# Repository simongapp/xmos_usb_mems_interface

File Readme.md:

# XMOS USB - MEMS microphone array audio interface
Hardware and firmware files for a MEMS microphones USB audio interface based on the XMOS XUF216. Allows to connect up to  16 microphones and provides the option to cascade multiple base boards.  

This work was done as part of my master's thesis at the TU Berlin, Department of Engineering Acoustics [https://www.akustik.tu-berlin.de/menue/home/parameter/en/](https://www.akustik.tu-berlin.de/menue/home/parameter/en/). The system was evaluated with the Acoular Framework for beamforming [http://www.acoular.org/](http://www.acoular.org/).

## Features
- Operates at 48kHz/24bit, with USB 2.0 (UAC2)
- One base board can process up to 16 MEMS microphones
- Cascade multiple baseboards by sharing a word clock or sync to external clock master
- Physically detached microphones, allows to add microphones in pairs of two
- Max. cable length between microphones and base board: 2.5m @ 48kHz
- Impedance matched clock and data transmission lines

## Folders
- 00PCB: EAGLE PCB files for the microphone PCBs and base board
- 01Firmware: XMOS firmware, port documentation and visualizations of the reference code

## Usage
- Clone to your local hard drive

- How to add the firmware files to xTimeComposer (based on https://gist.github.com/ahogen/93bf33ce47bb96c7fda60d844238fa43):  
  1. Link (but don't copy) projects and libraries from SVN dir into workspace
     1. File > Import > General > Existing Projects into Workspace
     2. Choose "Select root directory"
     3. Click "Browse" and navigate to the SVN dir where your projects and libraries were exported
     4. Click "Select All" to choose all projects and libraries
     5. Make sure "Copy projects into workspace" is not checked
     6. Finish

## Known issues
- Data transfer from the microphone boards to the base board leads to inverted data signals on the base board. Fixed by multiplying -1 on the PCM signals.
- No deterministic phase relationship between input and output of the CS2100. This results in a non-deterministic clock shift of up to 162.5ns@48kHz. Considered negligible with respect to the period of audio frequencies from 50ms(20Hz) to 42us(20kHz).
- The current firmware starts audio sampling as soon as the uC is ready, which leads to different buffer sizes and thus a delay of several samples at the host when using multiple base boards. Solution: Synchronize start of audio sampling to first SOF after device configuration. To be implemented in the future.

## License
MIT License

Copyright (c) 2021 Simon Gapp

Permission is hereby granted, free of charge, to any person obtaining a copy
of this software and associated documentation files (the "Software"), to deal
in the Software without restriction, including without limitation the rights
to use, copy, modify, merge, publish, distribute, sublicense, and/or sell
copies of the Software, and to permit persons to whom the Software is
furnished to do so, subject to the following conditions:

The above copyright notice and this permission notice shall be included in all
copies or substantial portions of the Software.

THE SOFTWARE IS PROVIDED "AS IS", WITHOUT WARRANTY OF ANY KIND, EXPRESS OR
IMPLIED, INCLUDING BUT NOT LIMITED TO THE WARRANTIES OF MERCHANTABILITY,
FITNESS FOR A PARTICULAR PURPOSE AND NONINFRINGEMENT. IN NO EVENT SHALL THE
AUTHORS OR COPYRIGHT HOLDERS BE LIABLE FOR ANY CLAIM, DAMAGES OR OTHER
LIABILITY, WHETHER IN AN ACTION OF CONTRACT, TORT OR OTHERWISE, ARISING FROM,
OUT OF OR IN CONNECTION WITH THE SOFTWARE OR THE USE OR OTHER DEALINGS IN THE
SOFTWARE.

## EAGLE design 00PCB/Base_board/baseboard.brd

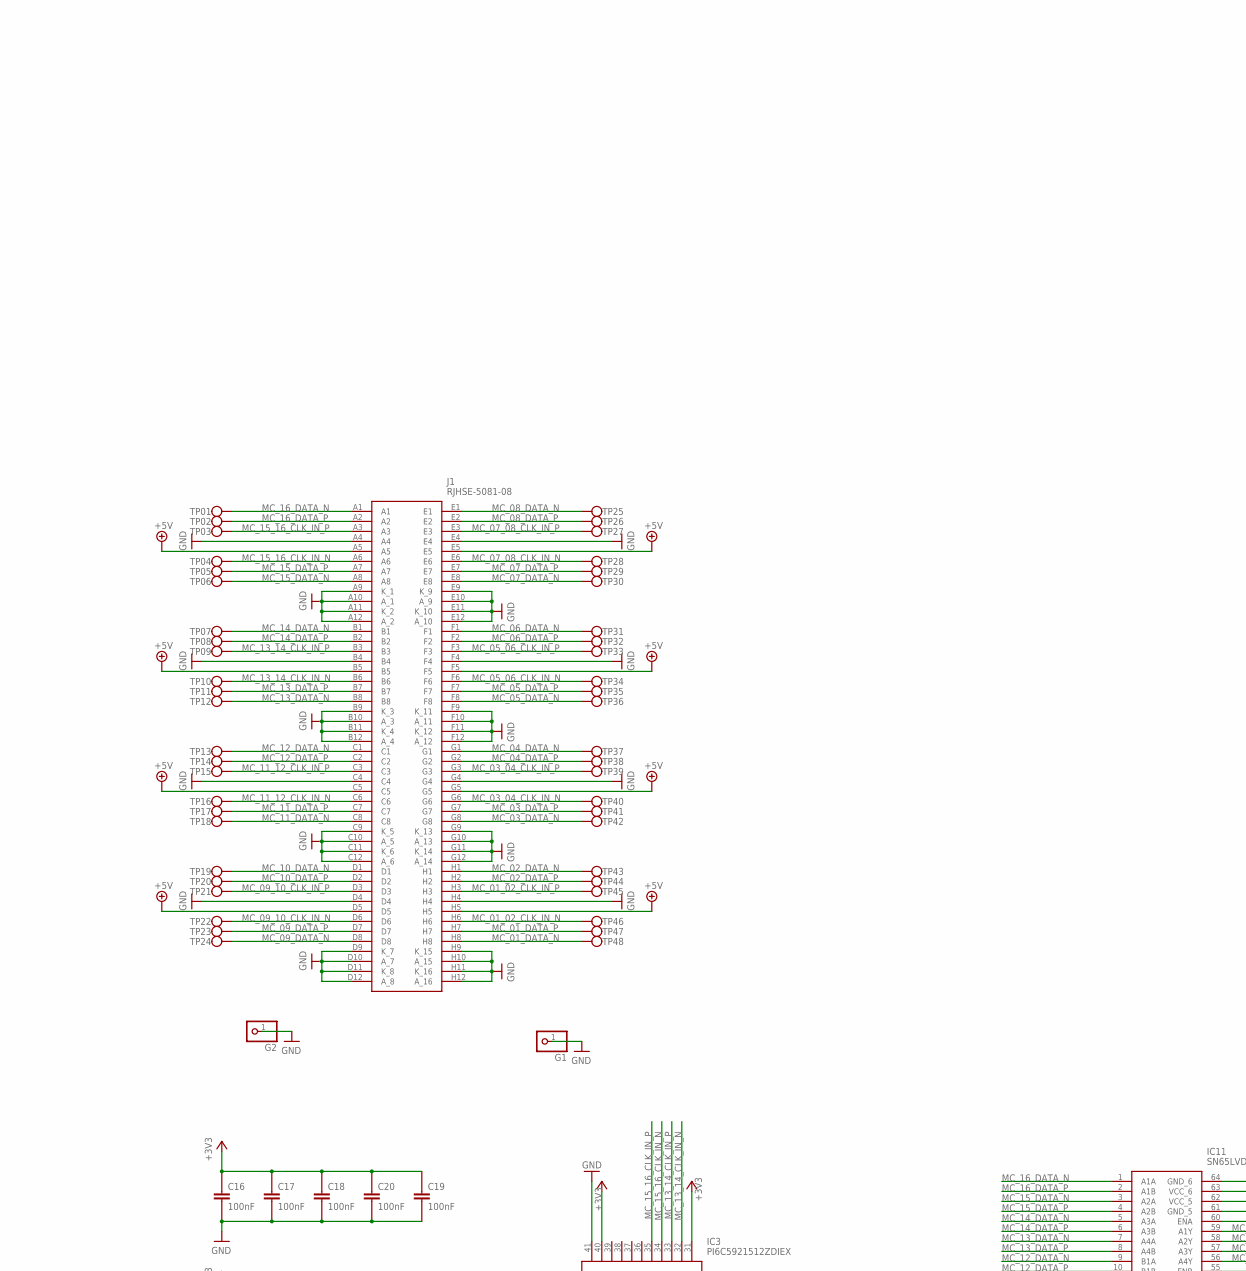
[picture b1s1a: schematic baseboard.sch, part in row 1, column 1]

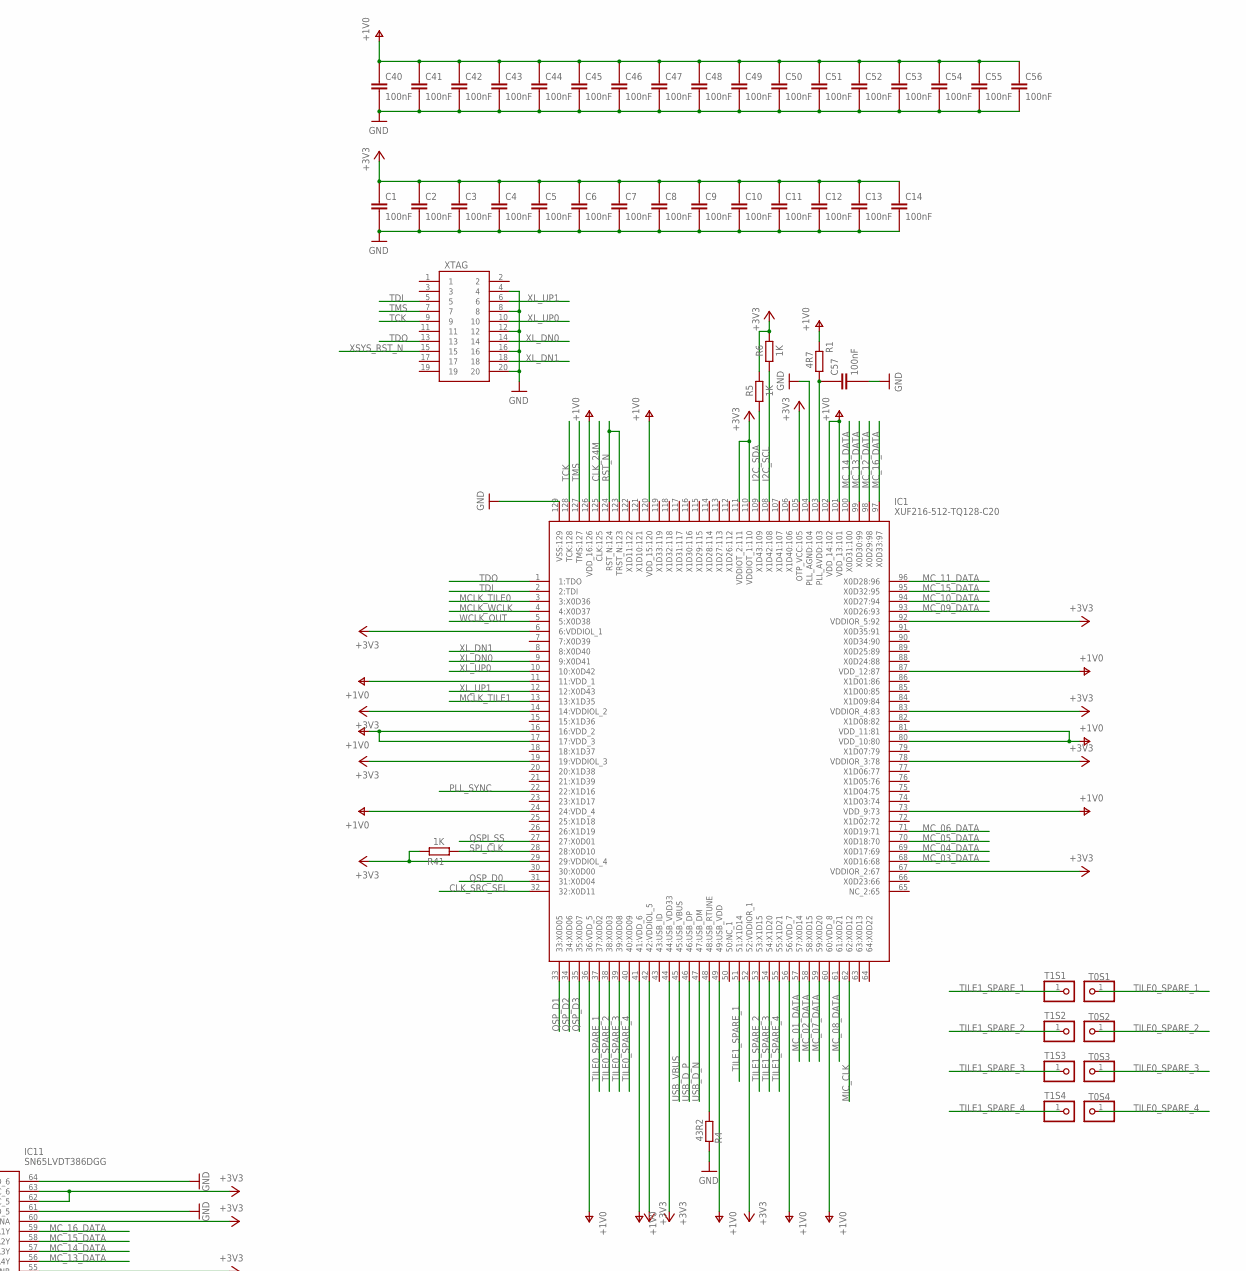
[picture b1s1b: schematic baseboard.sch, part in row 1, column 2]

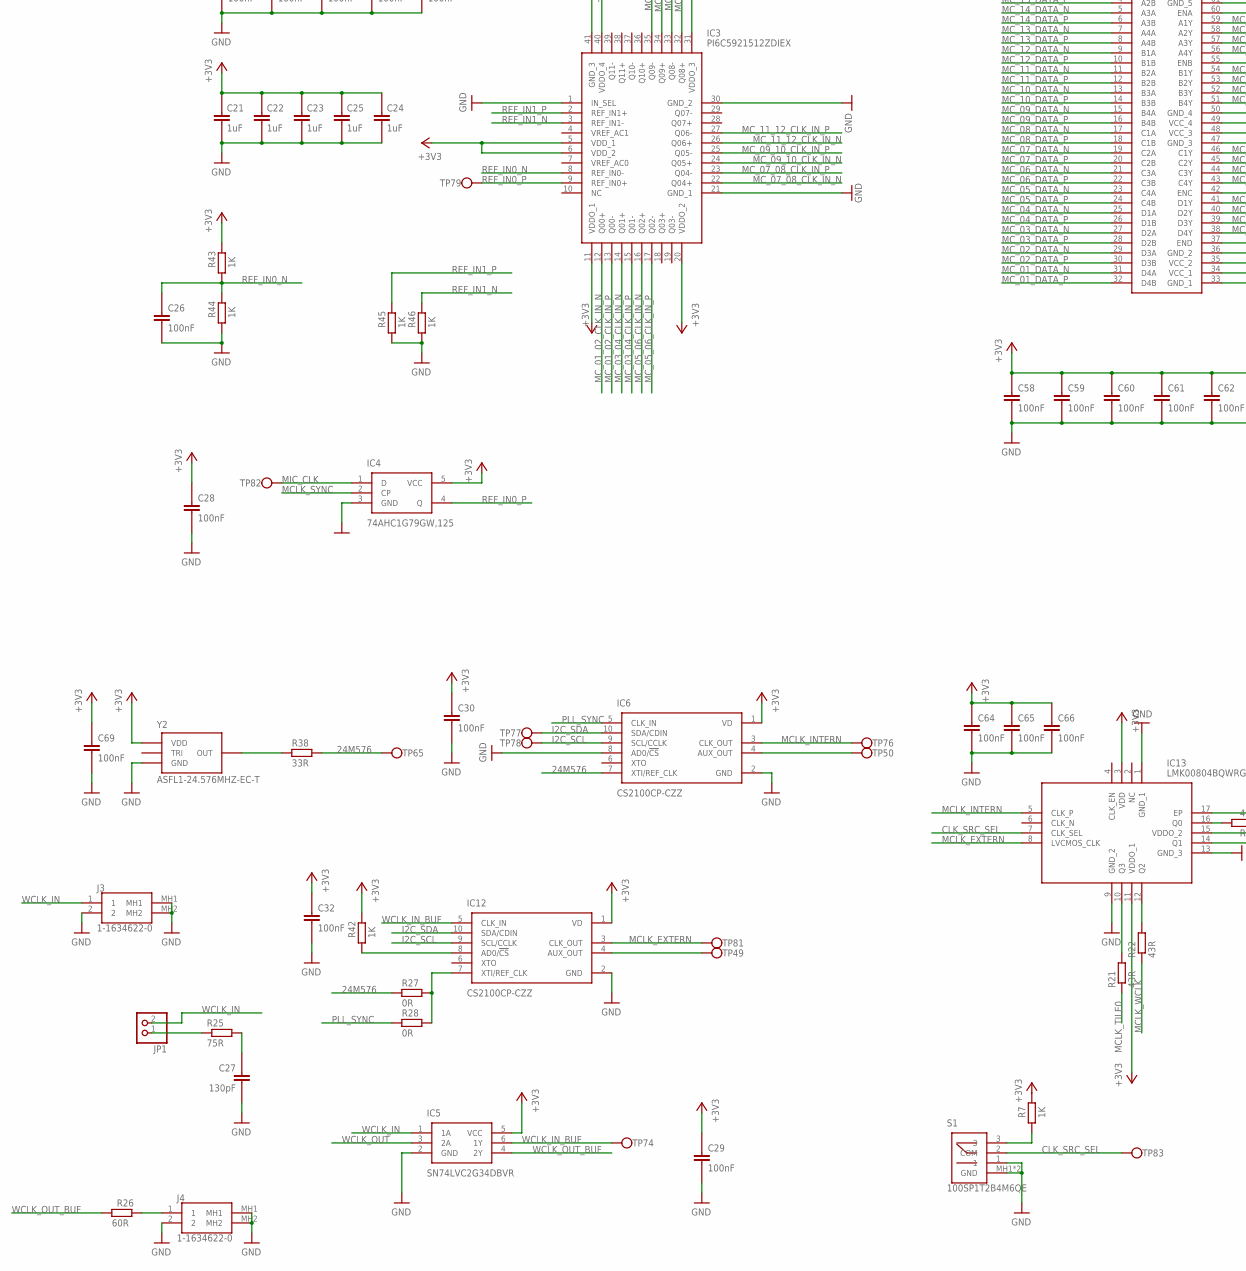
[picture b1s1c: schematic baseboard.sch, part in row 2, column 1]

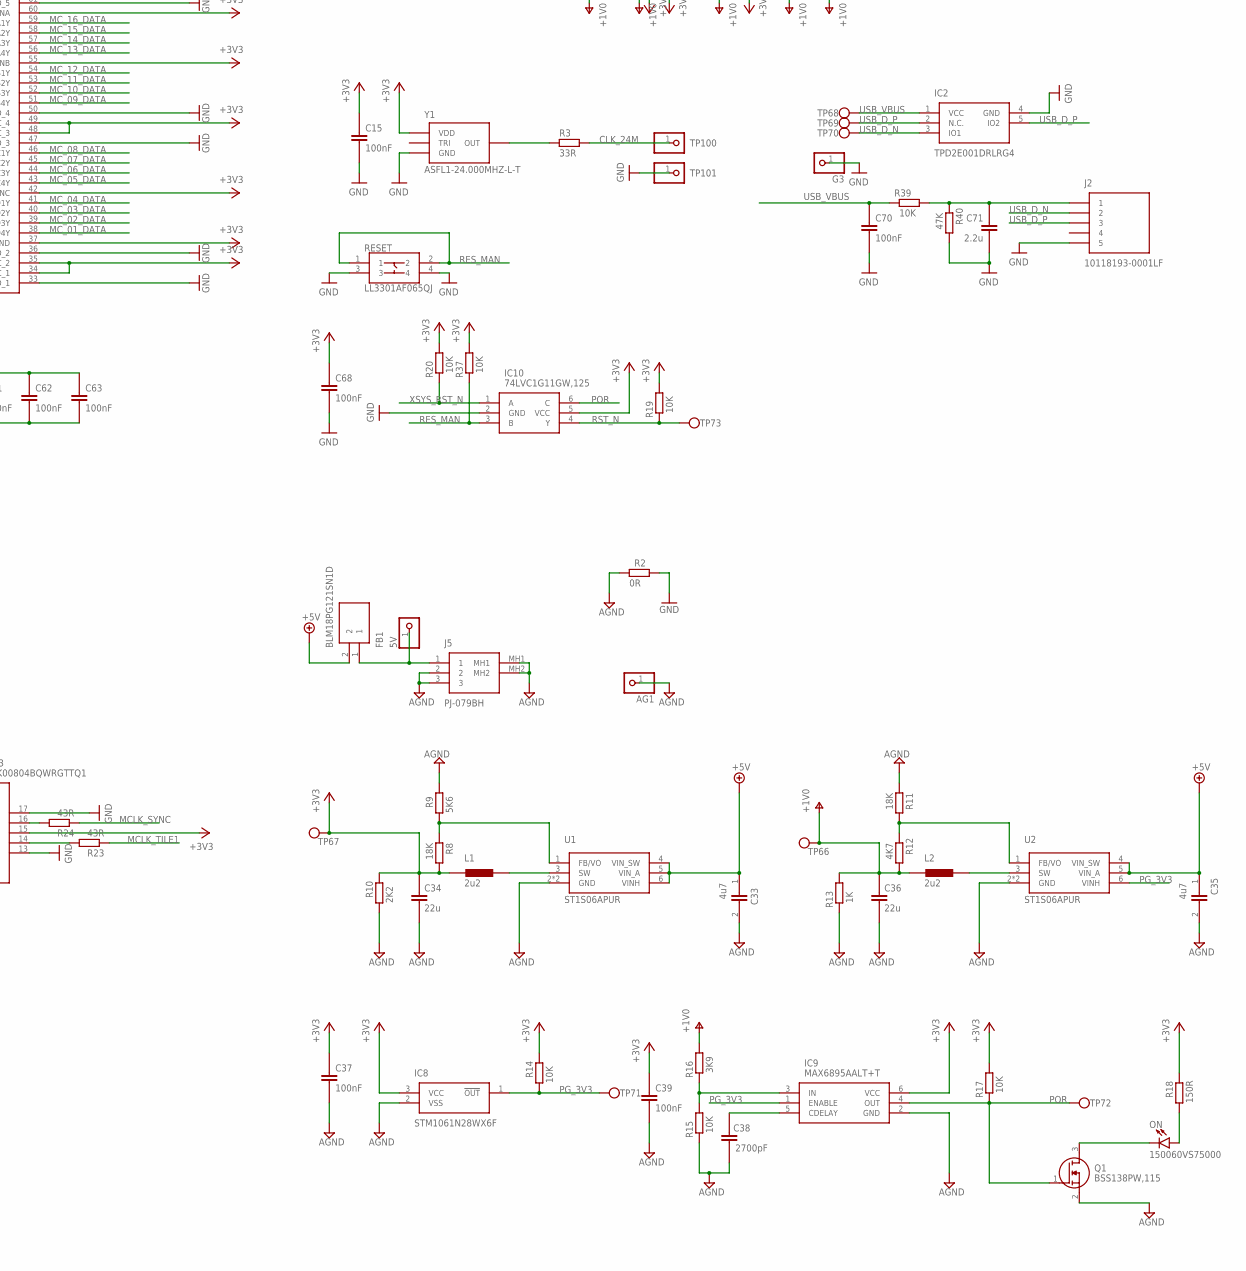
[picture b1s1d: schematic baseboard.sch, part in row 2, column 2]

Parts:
5V: PINHD-1X1; 1X01
AG1: PINHD-1X1; 1X01
C1, C2, C3, C4, C5, C6, C7, C8, C9, C10, C11, C12, C13, C14, C15, C16, C17, C18, C19, C20, C26, C28, C29, C30, C32, C37, C39, C40, C41, C42, C43, C44, C45, C46, C47, C48, C49, C50, C51, C52, C53, C54, C55, C56, C57, C58, C59, C60, C61, C62, C63, C64, C65, C66, C68, C69, C70: 100nF; CAPC1005X55N
C21, C22, C23, C24, C25: 1uF; CAPC1005X55N
C27: 130pF; CAPC1005X55N
C33, C35: 4u7; CAPC1005X55N
C34, C36: 22u; CAPC2012X145N
C38: 2N2; CAPC1005X55N
C71: GRM188R71A225KE15D; CAPC1608X90N
FB1: BLM18PG121SN1D; BEADC1608X95N
G1, G2, G3: PINHD-1X1; 1X01
IC1: XUF216-512-TQ128-C20; QFP40P1600X1600X120-129N
IC2: TPD2E001DRLRG4; SOTFL50P160X60-5N
IC3: PI6C5921512ZDIEX; QFN50P600X600X80-41N
IC4: 74AHC1G79GW,125; SOT65P212X110-5N
IC5: SN74LVC2G34DBVR; SOT95P280X145-6N
IC6, IC12: CS2100CP-CZZ; SOP50P490X110-10N
IC8: STM1061N28WX6F; SOT103P237X112-3N
IC9: MAX6895AALT+T; SON50P100X150X75-6N
IC10: 74LVC1G11GW,125; SOP65P210X110-6N
IC11: SN65LVDT386DGG; SOP50P810X120-64N
IC13: LMK00804BQWRGTTQ1; QFN50P300X300X100-17N
J1: RJHSE-5081-08; RJHSE508108
J2: 10118193-0001LF; 101181930001LF
J3, J4: 1-1634622-0; 116346220
J5: PJ-079BH; PJ079BH
JP1: PINHD-1X2; 1X02
L1, L2: NRH2412T2R2MNGH
ON: 150060VS75000; LEDC1608X80N
Q1: BSS138PW,115; SOT65P210X110-3N
R1: 4R7; RESC1005X40N
R2: 0R; RESC3116X65N
R3, R38: 33R; RESC1005X40N
R4: 43R2; RESC1005X40N
R5, R6, R7, R41, R42, R43, R44, R45, R46: 1K; RESC1005X40N
R8, R11: 18K; RESC2012X65N
R9: 5K6; RESC2012X70N
R10: 2K2; RESC2013X65N
R12: 4K7; RESC2013X65N
R13: AS08J1001ET; RESC2013X65N
R14, R15, R17, R19, R20, R37, R39: 10k; RESC1005X40N
R16: 3K9; RESC0402X15N
R18: 150R; RESC1005X40N
R21, R22, R23, R24: 43R; RESC1005X40N
R25, R26: 75R; RESC1005X40N
R27, R28: CRCW04020000Z0EDC; RESC1005X35N
R40: CRCW040247K0FKEDC; RESC1005X35N
RESET: LL3301AF065QJ; LL3301FF065QJ
S1: 100SP1T2B4M6QE
T0S1, T0S2, T0S3, T0S4, T1S1, T1S2, T1S3, T1S4: PINHD-1X1; 1X01
TP01, TP02, TP03, TP04, TP05, TP06, TP07, TP08, TP09, TP10, TP11, TP12, TP13, TP14, TP15, TP16, TP17, TP18, TP19, TP20, TP21, TP22, TP23, TP24, TP25, TP26, TP27, TP28, TP29, TP30, TP31, TP32, TP33, TP34, TP35, TP36, TP37, TP38, TP39, TP40, TP41, TP42, TP43, TP44, TP45, TP46, TP47, TP48, TP49, TP50, TP65, TP66, TP67, TP68, TP69, TP70, TP71, TP72, TP73, TP74, TP76, TP77, TP78, TP79, TP81, TP82, TP83: TESTPOINT_05_05; TP_05_05
TP100, TP101: PINHD-1X1; 1X01
U1, U2: ST1S06APUR; DFN6D
XTAG: 30320-5002HB; 303205002HB
Y1: ASFL1-24.000MHZ-L-T; ASFL-1
Y2: ASFL1-24.576MHZ-EC-T; ASFL-1

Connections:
24M576: IC6.7 (XTI/REF_CLK), R27.1, R38.2, TP65.TP
+3V3: C1.2, C2.2, C3.2, C4.2, C5.2, C6.2, C7.2, C8.2, C9.2, C10.2, C11.2, C12.2, C13.2, C14.2, C15.2, C16.2, C17.2, C18.2, C19.2, C20.2, C21.2, C22.2, C23.2, C24.2, C25.2, C28.2, C29.2, C30.2, C32.2, C34.2, C37.2, C39.2, C58.2, C59.2, C60.2, C61.2, C62.2, C63.2, C64.2, C65.2, C66.2, C68.2, C69.2, IC1.6 (6:VDDIOL_1), IC1.14 (14:VDDIOL_2), IC1.19 (19:VDDIOL_3), IC1.29 (29:VDDIOL_4), IC1.42 (42:VDDIOL_5), IC1.44 (44:USB_VDD33), IC1.52 (52:VDDIOR_1), IC1.67 (VDDIOR_2:67), IC1.78 (VDDIOR_3:78), IC1.83 (VDDIOR_4:83), IC1.92 (VDDIOR_5:92), IC1.105 (OTP_VCC:105), IC1.110 (VDDIOT_1:110), IC1.111 (VDDIOT_2:111), IC3.5 (VDD_1), IC3.6 (VDD_2), IC3.11 (VDDO_1), IC3.20 (VDDO_2), IC3.31 (VDDO_3), IC3.40 (VDDO_4), IC4.5 (VCC), IC5.5 (VCC), IC6.1 (VD), IC8.3 (VCC), IC9.6 (VCC), IC10.5 (VCC), IC11.34 (VCC_1), IC11.35 (VCC_2), IC11.37 (END), IC11.42 (ENC), IC11.48 (VCC_3), IC11.49 (VCC_4), IC11.55 (ENB), IC11.60 (ENA), IC11.62 (VCC_5), IC11.63 (VCC_6), IC12.1 (VD), IC13.3 (VDD), IC13.11 (VDDO_1), IC13.15 (VDDO_2), L1.1, R5.2, R6.2, R7.2, R8.2, R10.2, R14.2, R17.2, R18.2, R19.2, R20.2, R37.2, R41.2, R42.2, R43.2, TP67.TP, Y1.VDD, Y2.VDD
+5V: C33.1, C35.1, FB1.2, J1.A5, J1.B5, J1.C5, J1.D5, J1.E5, J1.F5, J1.G5, J1.H5, U1.4 (VIN_SW), U1.5 (VIN_A), U1.6 (VINH), U2.4 (VIN_SW), U2.5 (VIN_A)
AGND: AG1.1, C33.2, C34.1, C35.2, C36.1, C37.1, C38.2, C39.1, IC8.2 (VSS), IC9.2 (GND), J5.2, J5.3, J5.MH1, J5.MH2, Q1.2 (S), R2.1, R9.2, R10.1, R11.1, R13.1, R15.1, U1.2 (GND), U1.GND, U2.2 (GND), U2.GND
CLK_24M: IC1.125 (CLK:125), R3.2, TP100.1
CLK_SRC_SEL: IC1.32 (32:X0D11), IC13.7 (CLK_SEL), S1.2 (COM), TP83.TP
GND: C1.1, C2.1, C3.1, C4.1, C5.1, C6.1, C7.1, C8.1, C9.1, C10.1, C11.1, C12.1, C13.1, C14.1, C15.1, C16.1, C17.1, C18.1, C19.1, C20.1, C21.1, C22.1, C23.1, C24.1, C25.1, C26.1, C27.2, C28.1, C29.1, C30.1, C32.1, C40.1, C41.1, C42.1, C43.1, C44.1, C45.1, C46.1, C47.1, C48.1, C49.1, C50.1, C51.1, C52.1, C53.1, C54.1, C55.1, C56.1, C57.1, C58.1, C59.1, C60.1, C61.1, C62.1, C63.1, C64.1, C65.1, C66.1, C68.1, C69.1, C70.1, C71.2, G1.1, G2.1, G3.1, IC1.104 (PLL_AGND:104), IC1.129 (VSS:129), IC2.4 (GND), IC3.1 (IN_SEL), IC3.21 (GND_1), IC3.30 (GND_2), IC3.41 (GND_3), IC4.3 (GND), IC5.2 (GND), IC6.2 (GND), IC6.8 (AD0/!CS), IC10.2 (GND), IC11.33 (GND_1), IC11.36 (GND_2), IC11.47 (GND_3), IC11.50 (GND_4), IC11.61 (GND_5), IC11.64 (GND_6), IC12.2 (GND), IC13.1 (GND_1), IC13.9 (GND_2), IC13.13 (GND_3), IC13.17 (EP), J1.A4, J1.A9 (K_1), J1.A10 (A_1), J1.A11 (K_2), J1.A12 (A_2), J1.B4, J1.B9 (K_3), J1.B10 (A_3), J1.B11 (K_4), J1.B12 (A_4), J1.C4, J1.C9 (K_5), J1.C10 (A_5), J1.C11 (K_6), J1.C12 (A_6), J1.D4, J1.D9 (K_7), J1.D10 (A_7), J1.D11 (K_8), J1.D12 (A_8), J1.E4, J1.E9 (K_9), J1.E10 (A_9), J1.E11 (K_10), J1.E12 (A_10), J1.F4, J1.F9 (K_11), J1.F10 (A_11), J1.F11 (K_12), J1.F12 (A_12), J1.G4, J1.G9 (K_13), J1.G10 (A_13), J1.G11 (K_14), J1.G12 (A_14), J1.H4, J1.H9 (K_15), J1.H10 (A_15), J1.H11 (K_16), J1.H12 (A_16), J2.5, J2.MH1 (5), J2.MH2 (5), J2.MP1 (5), J2.MP2 (5), J2.MP3 (5), J2.MP4 (5), J3.2, J3.MH1, J3.MH2, J4.2, J4.MH1, J4.MH2, R2.2, R4.1, R40.2, R44.1, R45.1, R46.1, RESET.3, RESET.4, S1.1, S1.MH1 (GND), S1.MH2 (GND), TP101.1, XTAG.4, XTAG.8, XTAG.12, XTAG.16, XTAG.20, Y1.GND, Y2.GND
I2C_SCL: IC1.108 (X1D42:108), IC6.9 (SCL/CCLK), IC12.9 (SCL/CCLK), R6.1, TP78.TP
I2C_SDA: IC1.109 (X1D43:109), IC6.10 (SDA/CDIN), IC12.10 (SDA/CDIN), R5.1, TP77.TP
MCLK_EXTERN: IC12.3 (CLK_OUT), IC13.8 (LVCMOS_CLK), TP81.TP
MCLK_INTERN: IC6.3 (CLK_OUT), IC13.5 (CLK_P), TP76.TP
MCLK_SYNC: IC4.2 (CP), R24.1
MCLK_TILE0: IC1.3 (3:X0D36), R21.1
MCLK_TILE1: IC1.13 (13:X1D35), R23.1
MCLK_WCLK: IC1.4 (4:X0D37), R22.1
MC_01_02_CLK_IN_N: IC3.12 (Q00+), J1.H6, TP46.TP
MC_01_02_CLK_IN_P: IC3.13 (Q00-), J1.H3, TP45.TP
MC_01_DATA: IC1.57 (57:X0D14), IC11.38 (D4Y)
MC_01_DATA_N: IC11.31 (D4A), J1.H8, TP48.TP
MC_01_DATA_P: IC11.32 (D4B), J1.H7, TP47.TP
MC_02_DATA: IC1.58 (58:X0D15), IC11.39 (D3Y)
MC_02_DATA_N: IC11.29 (D3A), J1.H1, TP43.TP
MC_02_DATA_P: IC11.30 (D3B), J1.H2, TP44.TP
MC_03_04_CLK_IN_N: IC3.14 (Q01+), J1.G6, TP40.TP
MC_03_04_CLK_IN_P: IC3.15 (Q01-), J1.G3, TP39.TP
MC_03_DATA: IC1.68 (X0D16:68), IC11.40 (D2Y)
MC_03_DATA_N: IC11.27 (D2A), J1.G8, TP42.TP
MC_03_DATA_P: IC11.28 (D2B), J1.G7, TP41.TP
MC_04_DATA: IC1.69 (X0D17:69), IC11.41 (D1Y)
MC_04_DATA_N: IC11.25 (D1A), J1.G1, TP37.TP
MC_04_DATA_P: IC11.26 (D1B), J1.G2, TP38.TP
MC_05_06_CLK_IN_N: IC3.16 (Q02+), J1.F6, TP34.TP
MC_05_06_CLK_IN_P: IC3.17 (Q02-), J1.F3, TP33.TP
MC_05_DATA: IC1.70 (X0D18:70), IC11.43 (C4Y)
MC_05_DATA_N: IC11.23 (C4A), J1.F8, TP36.TP
MC_05_DATA_P: IC11.24 (C4B), J1.F7, TP35.TP
MC_06_DATA: IC1.71 (X0D19:71), IC11.44 (C3Y)
MC_06_DATA_N: IC11.21 (C3A), J1.F1, TP31.TP
MC_06_DATA_P: IC11.22 (C3B), J1.F2, TP32.TP
MC_07_08_CLK_IN_N: IC3.22 (Q04+), J1.E6, TP28.TP
MC_07_08_CLK_IN_P: IC3.23 (Q04-), J1.E3, TP27.TP
MC_07_DATA: IC1.59 (59:X0D20), IC11.45 (C2Y)
MC_07_DATA_N: IC11.19 (C2A), J1.E8, TP30.TP
MC_07_DATA_P: IC11.20 (C2B), J1.E7, TP29.TP
MC_08_DATA: IC1.61 (61:X0D21), IC11.46 (C1Y)
MC_08_DATA_N: IC11.17 (C1A), J1.E1, TP25.TP
MC_08_DATA_P: IC11.18 (C1B), J1.E2, TP26.TP
MC_09_10_CLK_IN_N: IC3.24 (Q05+), J1.D6, TP22.TP
MC_09_10_CLK_IN_P: IC3.25 (Q05-), J1.D3, TP21.TP
MC_09_DATA: IC1.93 (X0D26:93), IC11.51 (B4Y)
MC_09_DATA_N: IC11.15 (B4A), J1.D8, TP24.TP
MC_09_DATA_P: IC11.16 (B4B), J1.D7, TP23.TP
MC_10_DATA: IC1.94 (X0D27:94), IC11.52 (B3Y)
MC_10_DATA_N: IC11.13 (B3A), J1.D1, TP19.TP
MC_10_DATA_P: IC11.14 (B3B), J1.D2, TP20.TP
MC_11_12_CLK_IN_N: IC3.26 (Q06+), J1.C6, TP16.TP
MC_11_12_CLK_IN_P: IC3.27 (Q06-), J1.C3, TP15.TP
MC_11_DATA: IC1.96 (X0D28:96), IC11.53 (B2Y)
MC_11_DATA_N: IC11.11 (B2A), J1.C8, TP18.TP
MC_11_DATA_P: IC11.12 (B2B), J1.C7, TP17.TP
MC_12_DATA: IC1.98 (X0D29:98), IC11.54 (B1Y)
MC_12_DATA_N: IC11.9 (B1A), J1.C1, TP13.TP
MC_12_DATA_P: IC11.10 (B1B), J1.C2, TP14.TP
MC_13_14_CLK_IN_N: IC3.32 (Q08+), J1.B6, TP10.TP
MC_13_14_CLK_IN_P: IC3.33 (Q08-), J1.B3, TP09.TP
MC_13_DATA: IC1.99 (X0D30:99), IC11.56 (A4Y)
MC_13_DATA_N: IC11.7 (A4A), J1.B8, TP12.TP
MC_13_DATA_P: IC11.8 (A4B), J1.B7, TP11.TP
MC_14_DATA: IC1.100 (X0D31:100), IC11.57 (A3Y)
MC_14_DATA_N: IC11.5 (A3A), J1.B1, TP07.TP
MC_14_DATA_P: IC11.6 (A3B), J1.B2, TP08.TP
MC_15_16_CLK_IN_N: IC3.34 (Q09+), J1.A6, TP04.TP
MC_15_16_CLK_IN_P: IC3.35 (Q09-), J1.A3, TP03.TP
MC_15_DATA: IC1.95 (X0D32:95), IC11.58 (A2Y)
MC_15_DATA_N: IC11.3 (A2A), J1.A8, TP06.TP
MC_15_DATA_P: IC11.4 (A2B), J1.A7, TP05.TP
MC_16_DATA: IC1.97 (X0D33:97), IC11.59 (A1Y)
MC_16_DATA_N: IC11.1 (A1A), J1.A1, TP01.TP
MC_16_DATA_P: IC11.2 (A1B), J1.A2, TP02.TP
MIC_CLK: IC1.62 (62:X0D12), IC4.1 (D), TP82.TP
unnamed: IC1.48 (48:USB_RTUNE), R4.2
unnamed: R38.1, Y2.OUT
unnamed: R3.1, Y1.OUT
unnamed: C57.2, IC1.103 (PLL_AVDD:103), R1.2
unnamed: R7.1, S1.3
unnamed: C27.1, R25.2
unnamed: L1.2, U1.3 (SW)
unnamed: R8.1, R9.1, U1.1 (FB/VO)
unnamed: L2.2, U2.3 (SW)
unnamed: IC9.3 (IN), R15.2, R16.1
unnamed: ON.2 (A), R18.1
unnamed: R11.2, R12.1, U2.1 (FB/VO)
unnamed: C38.1, IC9.5 (CDELAY)
unnamed: ON.1 (K), Q1.3 (D)
unnamed: 5V.1, FB1.1, J5.1
unnamed: C71.1, J2.1, R39.2, R40.1
unnamed: IC12.8 (AD0/!CS), R42.1
unnamed: IC12.4 (AUX_OUT), TP49.TP
unnamed: JP1.1, R25.1
unnamed: IC6.4 (AUX_OUT), TP50.TP
unnamed: IC12.7 (XTI/REF_CLK), R27.2, R28.2
unnamed: IC13.16 (Q0), R24.2
unnamed: IC13.14 (Q1), R23.2
unnamed: IC13.12 (Q2), R22.2
unnamed: IC13.10 (Q3), R21.2
unnamed: J4.1, R26.2
PG_3V3: IC8.1 (!OUT), IC9.1 (ENABLE), R14.1, TP71.TP, U2.6 (VINH)
PLL_SYNC: IC1.22 (22:X1D16), IC6.5 (CLK_IN), R28.1
POR: IC9.4 (OUT), IC10.6 (C), Q1.1 (G), R17.1, TP72.TP
QSPI_SS: IC1.27 (27:X0D01)
QSP_D0: IC1.31 (31:X0D04)
QSP_D1: IC1.33 (33:X0D05)
QSP_D2: IC1.34 (34:X0D06)
QSP_D3: IC1.35 (35:X0D07)
REF_IN0_N: C26.2, IC3.8 (REF_IN0-), R43.1, R44.2
REF_IN0_P: IC3.9 (REF_IN0+), IC4.4 (Q), TP79.TP
REF_IN1_N: IC3.3 (REF_IN1-), R46.2
REF_IN1_P: IC3.2 (REF_IN1+), R45.2
RES_MAN: IC10.3 (B), R37.1, RESET.1, RESET.2
RST_N: IC1.123 (TRST_N:123), IC1.124 (RST_N:124), IC10.4 (Y), R19.1, TP73.TP
SPI_CLK: IC1.28 (28:X0D10), R41.1
TCK: IC1.128 (TCK:128), XTAG.9
TDI: IC1.2 (2:TDI), XTAG.5
TDO: IC1.1 (1:TDO), XTAG.13
TILE0_SPARE_1: IC1.37 (37:X0D02), T0S1.1
TILE0_SPARE_2: IC1.38 (38:X0D03), T0S2.1
TILE0_SPARE_3: IC1.39 (39:X0D08), T0S3.1
TILE0_SPARE_4: IC1.40 (40:X0D09), T0S4.1
TILE1_SPARE_1: IC1.51 (51:X1D14), T1S1.1
TILE1_SPARE_2: IC1.53 (53:X1D15), T1S2.1
TILE1_SPARE_3: IC1.54 (54:X1D20), T1S3.1
TILE1_SPARE_4: IC1.55 (55:X1D21), T1S4.1
TMS: IC1.127 (TMS:127), XTAG.7
USB_D_N: IC1.47 (47:USB_DM), IC2.3 (IO1), J2.2, TP70.TP
USB_D_P: IC1.46 (46:USB_DP), IC2.2 (N.C.), IC2.5 (IO2), J2.3, TP69.TP
USB_VBUS: C70.2, IC1.45 (45:USB_VBUS), IC2.1 (VCC), R39.1, TP68.TP
V+: C36.2, C40.2, C41.2, C42.2, C43.2, C44.2, C45.2, C46.2, C47.2, C48.2, C49.2, C50.2, C51.2, C52.2, C53.2, C54.2, C55.2, C56.2, IC1.11 (11:VDD_1), IC1.16 (16:VDD_2), IC1.17 (17:VDD_3), IC1.24 (24:VDD_4), IC1.36 (36:VDD_5), IC1.41 (41:VDD_6), IC1.49 (49:USB_VDD), IC1.56 (56:VDD_7), IC1.60 (60:VDD_8), IC1.73 (VDD_9:73), IC1.80 (VDD_10:80), IC1.81 (VDD_11:81), IC1.87 (VDD_12:87), IC1.101 (VDD_13:101), IC1.102 (VDD_14:102), IC1.120 (VDD_15:120), IC1.126 (VDD_16:126), L2.1, R1.1, R12.2, R13.2, R16.2, TP66.TP
WCLK_IN: IC5.1 (1A), J3.1, JP1.2
WCLK_IN_BUF: IC5.6 (1Y), IC12.5 (CLK_IN), TP74.TP
WCLK_OUT: IC1.5 (5:X0D38), IC5.3 (2A)
WCLK_OUT_BUF: IC5.4 (2Y), R26.1
XL_DN0: IC1.9 (9:X0D41), XTAG.14
XL_DN1: IC1.8 (8:X0D40), XTAG.18
XL_UP0: IC1.10 (10:X0D42), XTAG.10
XL_UP1: IC1.12 (12:X0D43), XTAG.6
XSYS_RST_N: IC10.1 (A), R20.1, XTAG.15

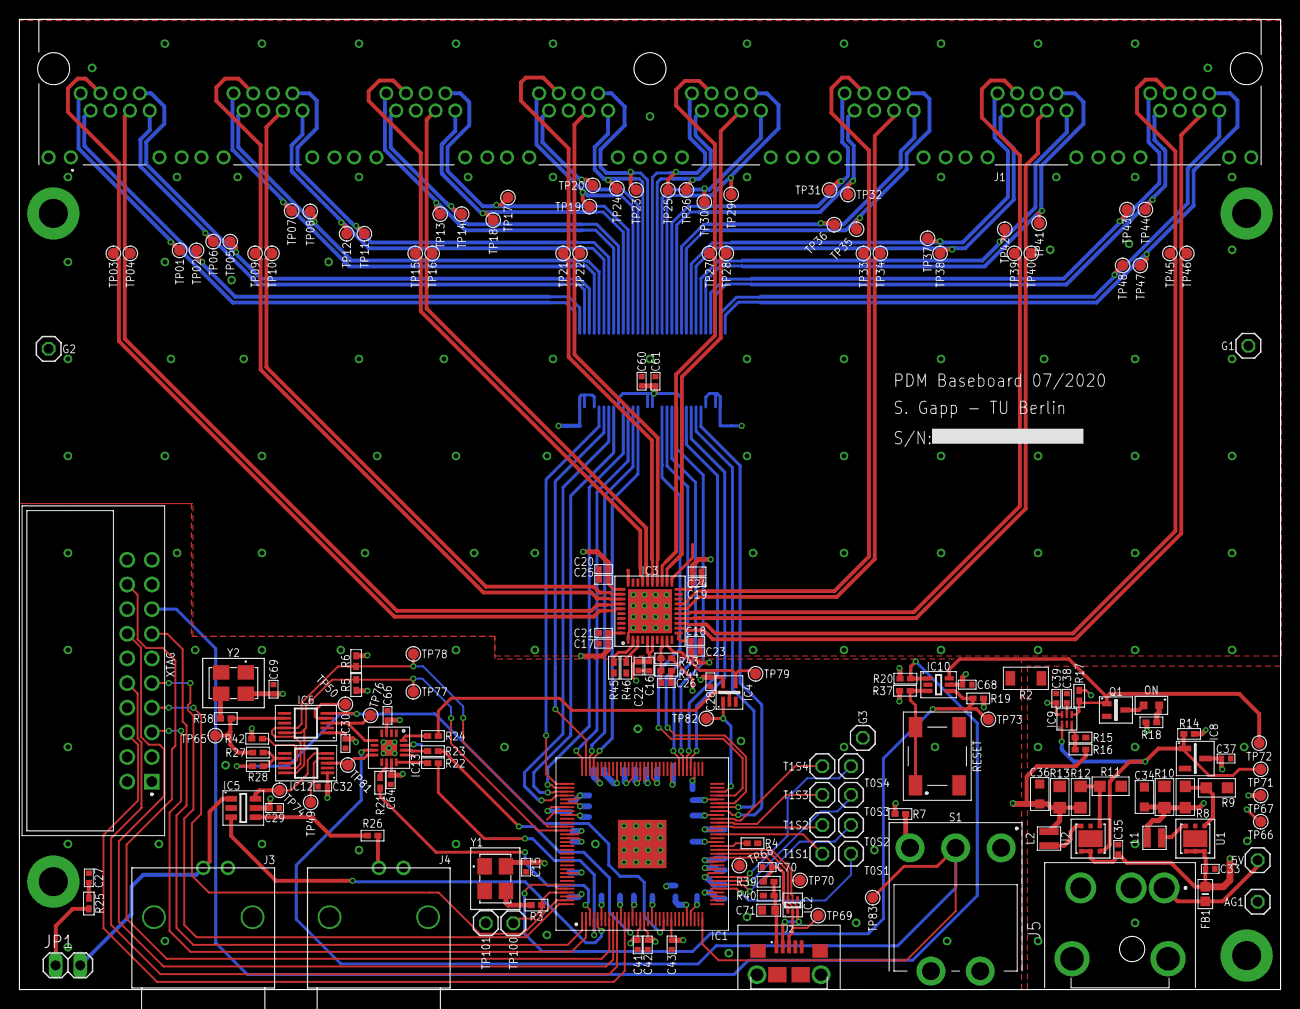
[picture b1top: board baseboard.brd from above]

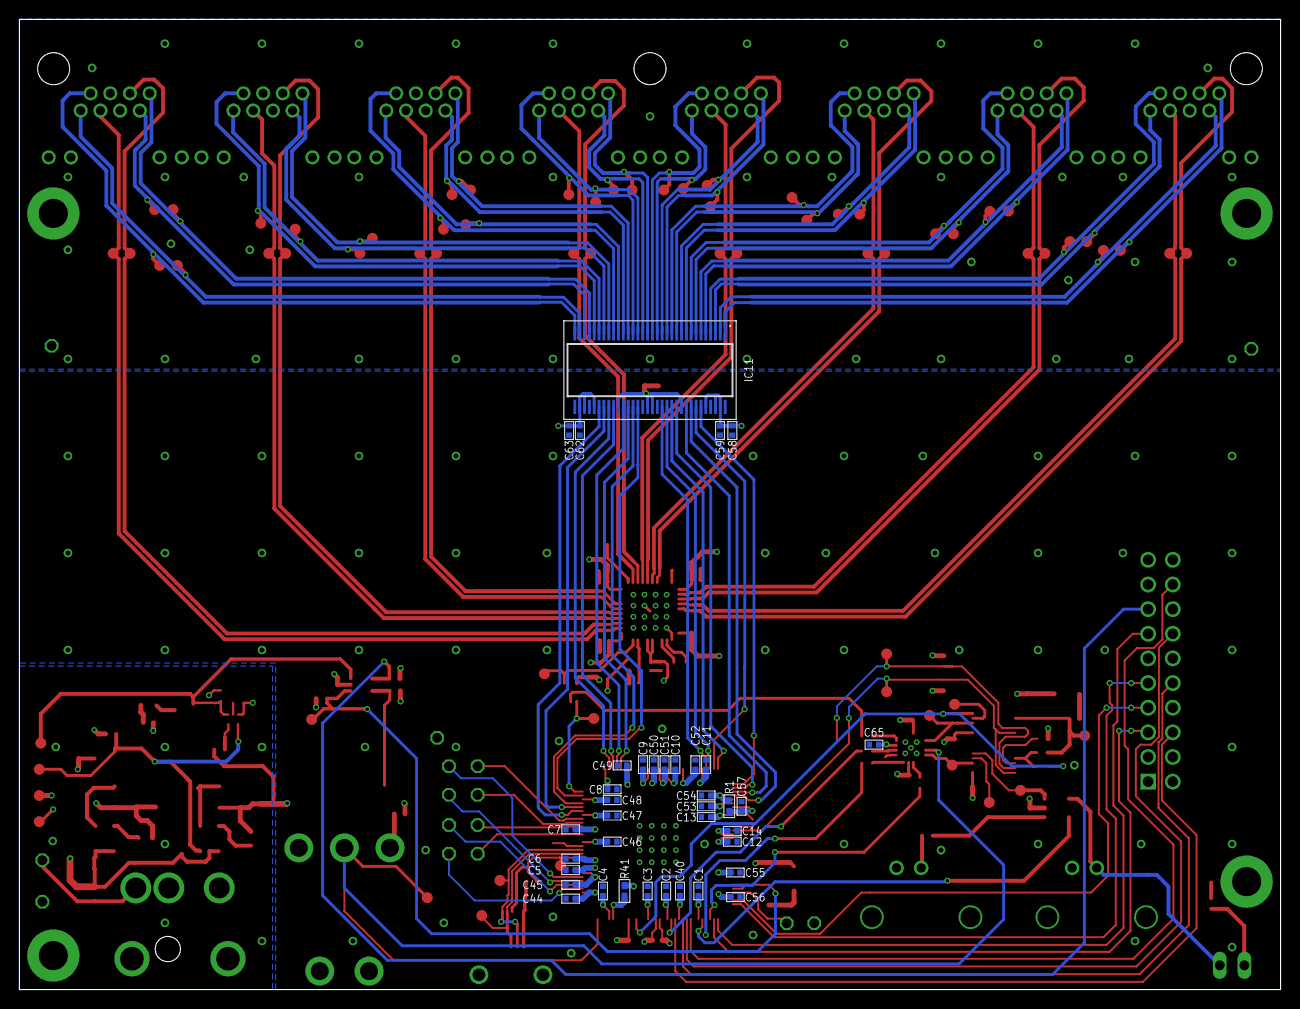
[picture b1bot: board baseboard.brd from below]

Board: 4 copper layers, 130.0 x 100.0 mm, 219 parts (37 on the bottom side), 141 nets.

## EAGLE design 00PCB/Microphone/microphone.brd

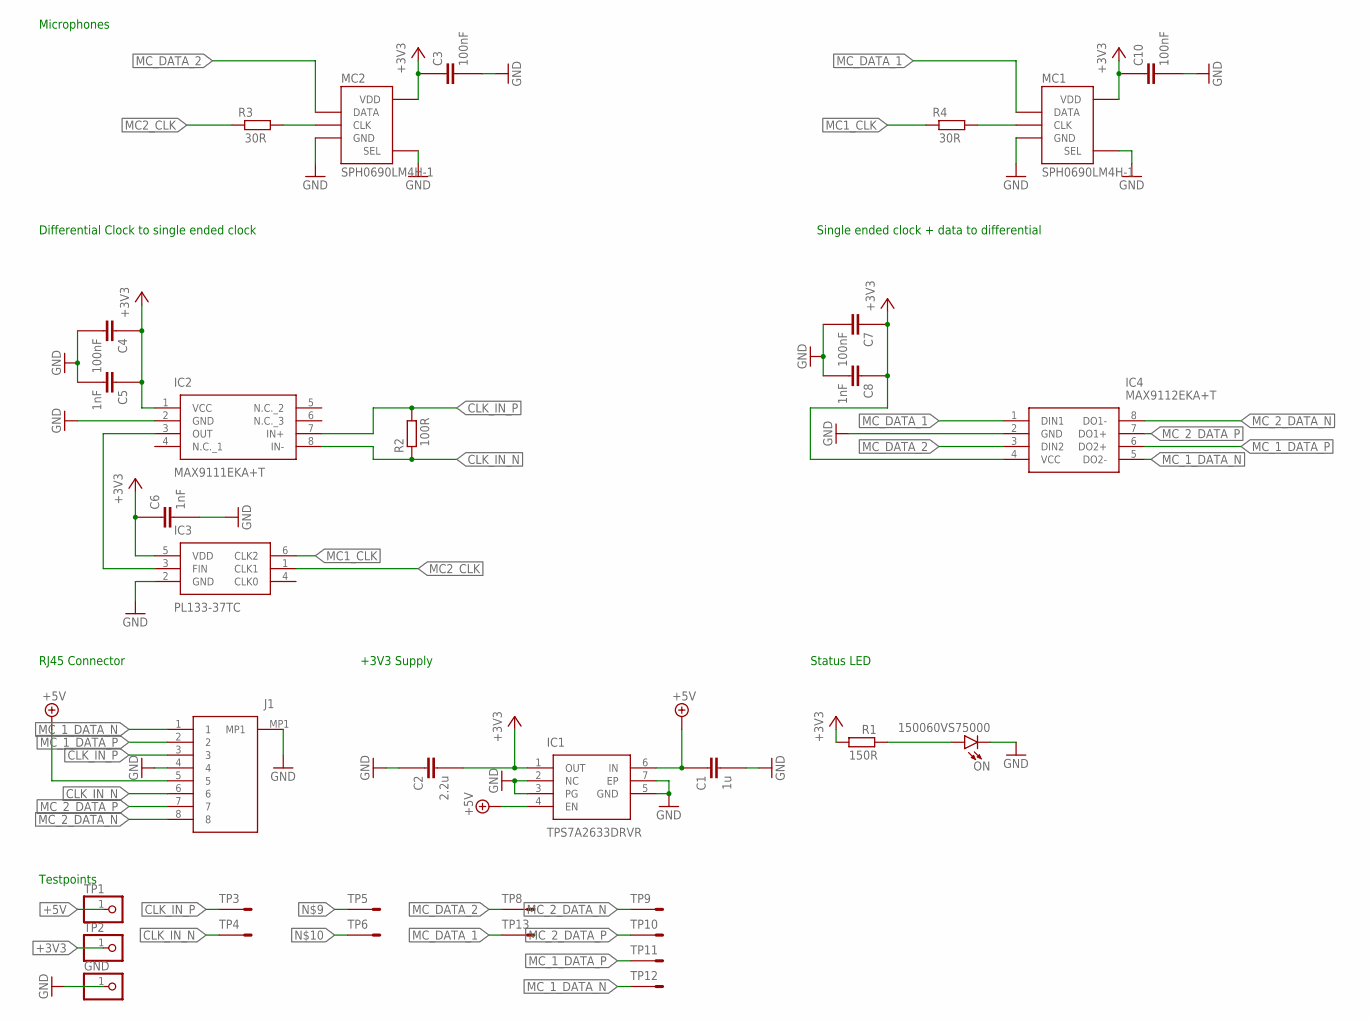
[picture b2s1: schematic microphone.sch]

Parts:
C1: 1u; CAPC1608X90N
C2: 2.2u; CAPC1608X90N
C3, C4, C7, C10: 100nF; CAPC1005X55N
C5, C6, C8: 1nF; CAPC1005X56N
GND: PINHD-1X1; 1X01
IC1: TPS7A2633DRVR
IC2: MAX9111EKA+T; SOT65P280X145-8N
IC3: PL133-37TC; SOT95P280X135-6N
IC4: MAX9112EKA+T; SOT65P280X145-8N
J1: RJE231883116T
MC1, MC2: SPH0690LM4H-1
ON: 150060VS75000; LEDC1608X80N
R1: 150; RESC1005X40N
R2: RT0402FRE07100RL; RESC1005X8N
R3, R4: 100nF; RESC1005X40N
TP1, TP2: PINHD-1X1; 1X01
TP3, TP4, TP5, TP6, TP8, TP9, TP10, TP11, TP12, TP13: TESTPOINT_05_05; TP_05_05

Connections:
+3V3: C2.2, C3.1, C4.1, C5.1, C6.1, C7.1, C8.1, C10.1, IC1.1 (OUT), IC2.1 (VCC), IC3.5 (VDD), IC4.4 (VCC), MC1.VDD, MC2.VDD, R1.1, TP2.1
+5V: C1.1, IC1.4 (EN), IC1.6 (IN), J1.5, TP1.1
CLK_IN_N: IC2.8 (IN-), J1.6, R2.1, TP4.TP
CLK_IN_P: IC2.7 (IN+), J1.3, R2.2, TP3.TP
GND: C1.2, C2.1, C3.2, C4.2, C5.2, C6.2, C7.2, C8.2, C10.2, GND.1, IC1.2 (NC), IC1.3 (PG), IC1.5 (GND), IC1.7 (EP), IC2.2 (GND), IC3.2 (GND), IC4.2 (GND), J1.4, J1.MP1, MC1.GND, MC1.SEL, MC2.GND, MC2.SEL, ON.1 (K)
MC1_CLK: IC3.6 (CLK2), R4.1
MC2_CLK: IC3.1 (CLK1), R3.1
MC_1_DATA_N: IC4.5 (DO2-), J1.1, TP12.TP
MC_1_DATA_P: IC4.6 (DO2+), J1.2, TP11.TP
MC_2_DATA_N: IC4.8 (DO1-), J1.8, TP9.TP
MC_2_DATA_P: IC4.7 (DO1+), J1.7, TP10.TP
MC_DATA_1: IC4.1 (DIN1), MC1.DATA, TP13.TP
MC_DATA_2: IC4.3 (DIN2), MC2.DATA, TP8.TP
unnamed: ON.2 (A), R1.2
unnamed: IC2.3 (OUT), IC3.3 (FIN)
unnamed: MC2.CLK, R3.2, TP5.TP
unnamed: MC1.CLK, R4.2, TP6.TP

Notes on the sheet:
RJ45 Connector
+3V3 Supply
Differential Clock to single ended clock
Single ended clock + data to differential
Microphones
Status LED
Testpoints

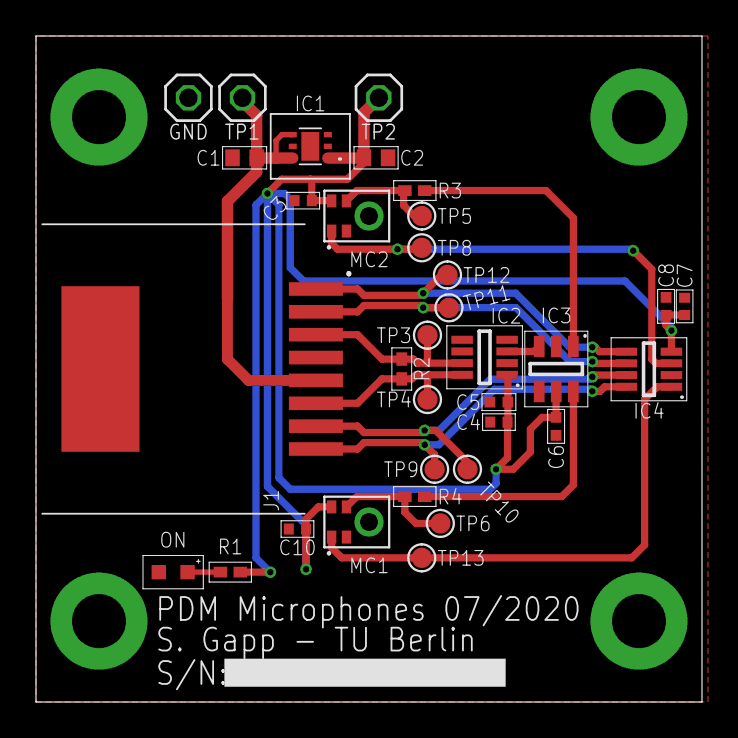
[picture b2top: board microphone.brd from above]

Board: 2 copper layers, 37.0 x 37.0 mm, 34 parts (0 on the bottom side), 17 nets.

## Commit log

2021-02-11 updates Readme
2021-02-26 adds Thesis
